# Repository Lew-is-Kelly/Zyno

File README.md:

# Zyno
My own ergo split keyboard layout

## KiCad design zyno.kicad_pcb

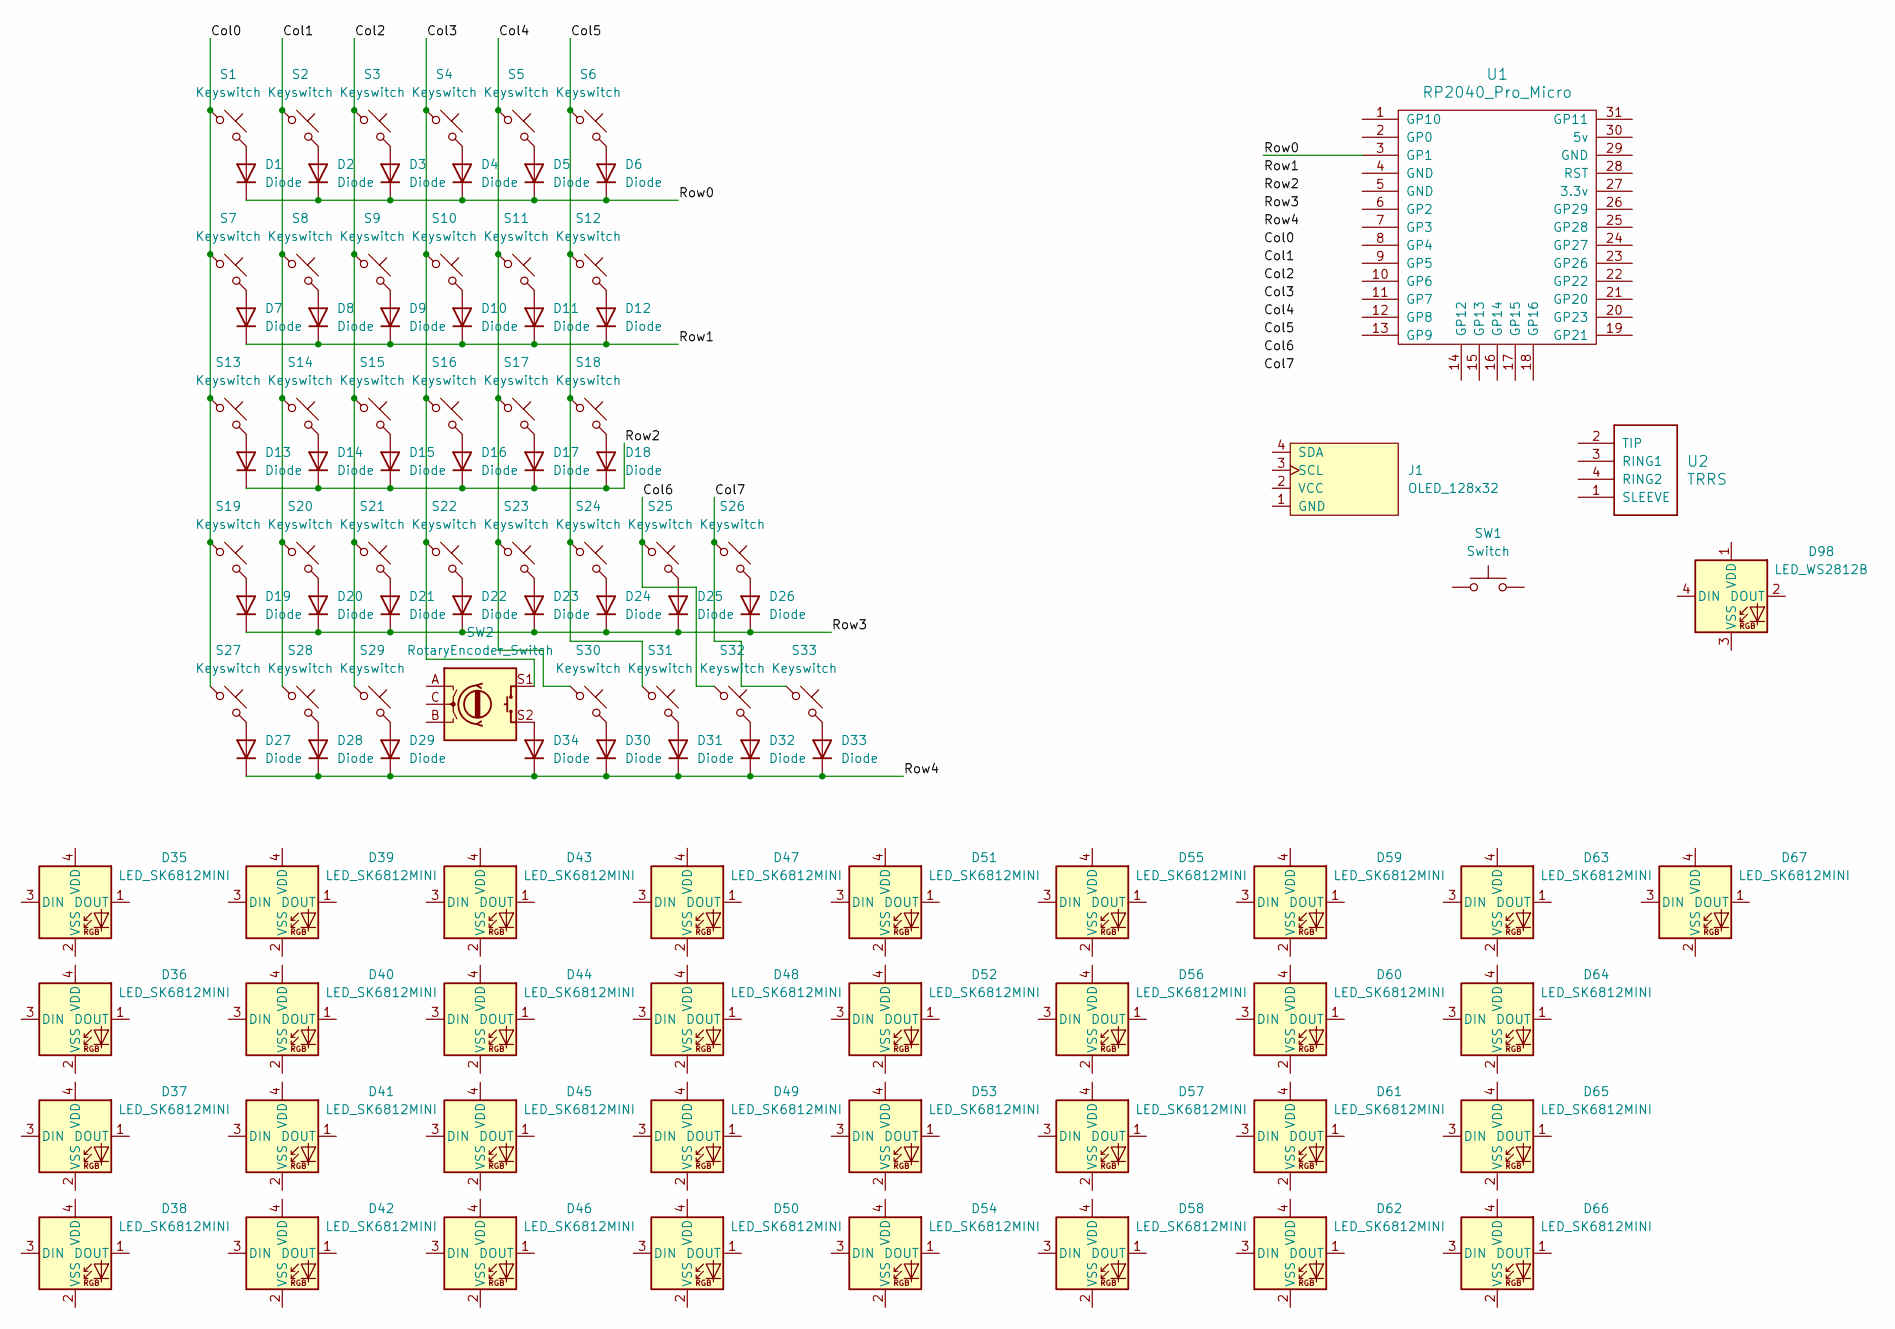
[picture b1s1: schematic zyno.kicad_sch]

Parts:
D1, D2, D3, D4, D5, D6, D7, D8, D9, D10, D11, D12, D13, D14, D15, D16, D17, D18, D19, D20, D21, D22, D23, D24, D25, D26, D27, D28, D29, D30, D31, D32, D33, D34: Diode; Diode_SOD-123
D35, D36, D37, D38, D39, D40, D41, D42, D43, D44, D45, D46, D47, D48, D49, D50, D51, D52, D53, D54, D55, D56, D57, D58, D59, D60, D61, D62, D63, D64, D65, D66, D67: LED_SK6812MINI
D98: LED_WS2812B
J1: OLED_128x32
S1, S2, S3, S4, S5, S6, S7, S8, S9, S10, S11, S12, S13, S14, S15, S16, S17, S18, S19, S20, S21, S22, S23, S24, S25, S26, S27, S28, S29, S30: Keyswitch; Hotswap_Choc_V1V2_1.00u
S31, S32, S33: Keyswitch; Hotswap_Choc_V1V2_1.50u_90deg
SW1: Switch; Button_MJTP1243
SW2: RotaryEncoder_Switch; RotaryEncoder_Alps_EC11E-Switch_Vertical_H20mm
U1: RP2040_Pro_Micro
U2: TRRS; TRRS_PJ-320A

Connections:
/Row0: D1.1 (K), D2.1 (K), D3.1 (K), D4.1 (K), D5.1 (K), D6.1 (K), U1.3 (GP1)
/Row1: D7.1 (K), D8.1 (K), D9.1 (K), D10.1 (K), D11.1 (K), D12.1 (K)
/Row2: D13.1 (K), D14.1 (K), D15.1 (K), D16.1 (K), D17.1 (K), D18.1 (K)
/Row3: D19.1 (K), D20.1 (K), D21.1 (K), D22.1 (K), D23.1 (K), D24.1 (K), D25.1 (K), D26.1 (K)
/Row4: D27.1 (K), D28.1 (K), D29.1 (K), D30.1 (K), D31.1 (K), D32.1 (K), D33.1 (K), D34.1 (K)
unnamed: D1.2 (A), S1.2
unnamed: D2.2 (A), S2.2
unnamed: D3.2 (A), S3.2
unnamed: D4.2 (A), S4.2
unnamed: D5.2 (A), S5.2
unnamed: D6.2 (A), S6.2
unnamed: D7.2 (A), S7.2
unnamed: D8.2 (A), S8.2
unnamed: D9.2 (A), S9.2
unnamed: D10.2 (A), S10.2
unnamed: D11.2 (A), S11.2
unnamed: D12.2 (A), S12.2
unnamed: D13.2 (A), S13.2
unnamed: D14.2 (A), S14.2
unnamed: D15.2 (A), S15.2
unnamed: D16.2 (A), S16.2
unnamed: D17.2 (A), S17.2
unnamed: D18.2 (A), S18.2
unnamed: D19.2 (A), S19.2
unnamed: D20.2 (A), S20.2
unnamed: D21.2 (A), S21.2
unnamed: D22.2 (A), S22.2
unnamed: D23.2 (A), S23.2
unnamed: D24.2 (A), S24.2
unnamed: D25.2 (A), S25.2
unnamed: D26.2 (A), S26.2
unnamed: D27.2 (A), S27.2
unnamed: D28.2 (A), S28.2
unnamed: D29.2 (A), S29.2
unnamed: D30.2 (A), S30.2
unnamed: D31.2 (A), S31.2
unnamed: D32.2 (A), S32.2
unnamed: D33.2 (A), S33.2
unnamed: D34.2 (A), SW2.S2
unnamed: S1.1, S7.1, S13.1, S19.1, S27.1
unnamed: S4.1, S10.1, S16.1, S22.1, SW2.S1
unnamed: S5.1, S11.1, S17.1, S23.1, S30.1
unnamed: S6.1, S12.1, S18.1, S24.1, S31.1
unnamed: S2.1, S8.1, S14.1, S20.1, S28.1
unnamed: S3.1, S9.1, S15.1, S21.1, S29.1
unnamed: S25.1, S32.1
unnamed: S26.1, S33.1

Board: 2 copper layers, 106 parts (67 on the bottom side), 47 nets, no tracks yet.

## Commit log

2024-05-10 Initial Commit, adding files made before repo
2024-05-11 Linked Schematic
2024-08-16 added ergogen files
2024-08-16 trail generation of ergogen
2024-08-17 ergogen done?
2024-08-17 More work...
2024-08-18 PCB's done
